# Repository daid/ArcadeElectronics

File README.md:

ArcadeElectronics
=================

V-USB based Electronics board for Arcade controls

Features
========
* V-USB based USB Interface emulating a mouse, keyboard and gamepad with full configuration of button mapping (no drivers required)
* 4 way digital joystick + 7 button connections. 4 way joystick inputs can also be used for analogue joystick.
* 16 LED output pins (max current total 200mA) which can also be used as inputs. And 8 are also mapped wired to 1A higher power outputs with external power supply (optional hardware)
* RFM12 wireless transiever (optional hardware) allows communication with other controllers and building of wireless controllers with 2 boards.
* Full open-source hardware & open-source software - Build with Free-Open-Source tools (KiCAD & AVR-GCC)
* ISP header to program the AVR (reset line can be cut and re-wired to have the board function as an programmer on the same header)
* USB-micro or USB-B connector depending on your taste
* Different small board designs, depending on your requirements:
	* 100x50mm: Fully featured, has option for 16 LED outputs, of which 8 can be configured for high power. Has wireless RFM12 option. 4 direction inputs, 7 button inputs
	* 50x50mm: Only base features with screw connectors. 4 direction inputs, 7 button inputs.
	* 50x25mm: Only base features with pin connectors. 4 direction inputs, 7 button inputs 
	* 25x25mm: Only base features with pin connectors, components on both sides. 4 direction inputs, 7 button inputs 

Organization
============
The following directories are in this project:
* Electronics - Contain the KiCAD design files
* Software/firmware/bootloader - Modified HIDBoot
* Software/firmware/arcade - Main firmware for the Arcade controller
* Software/computer/commandline - Commandline application to change the controller configuration, and control the LEDs
* Software/computer/lib - Library shared between different applications for custom commands to the ArcadeController
* Software/computer/gui_test - SDL based application to verify the Keyboard/Joystick/Mouse inputs

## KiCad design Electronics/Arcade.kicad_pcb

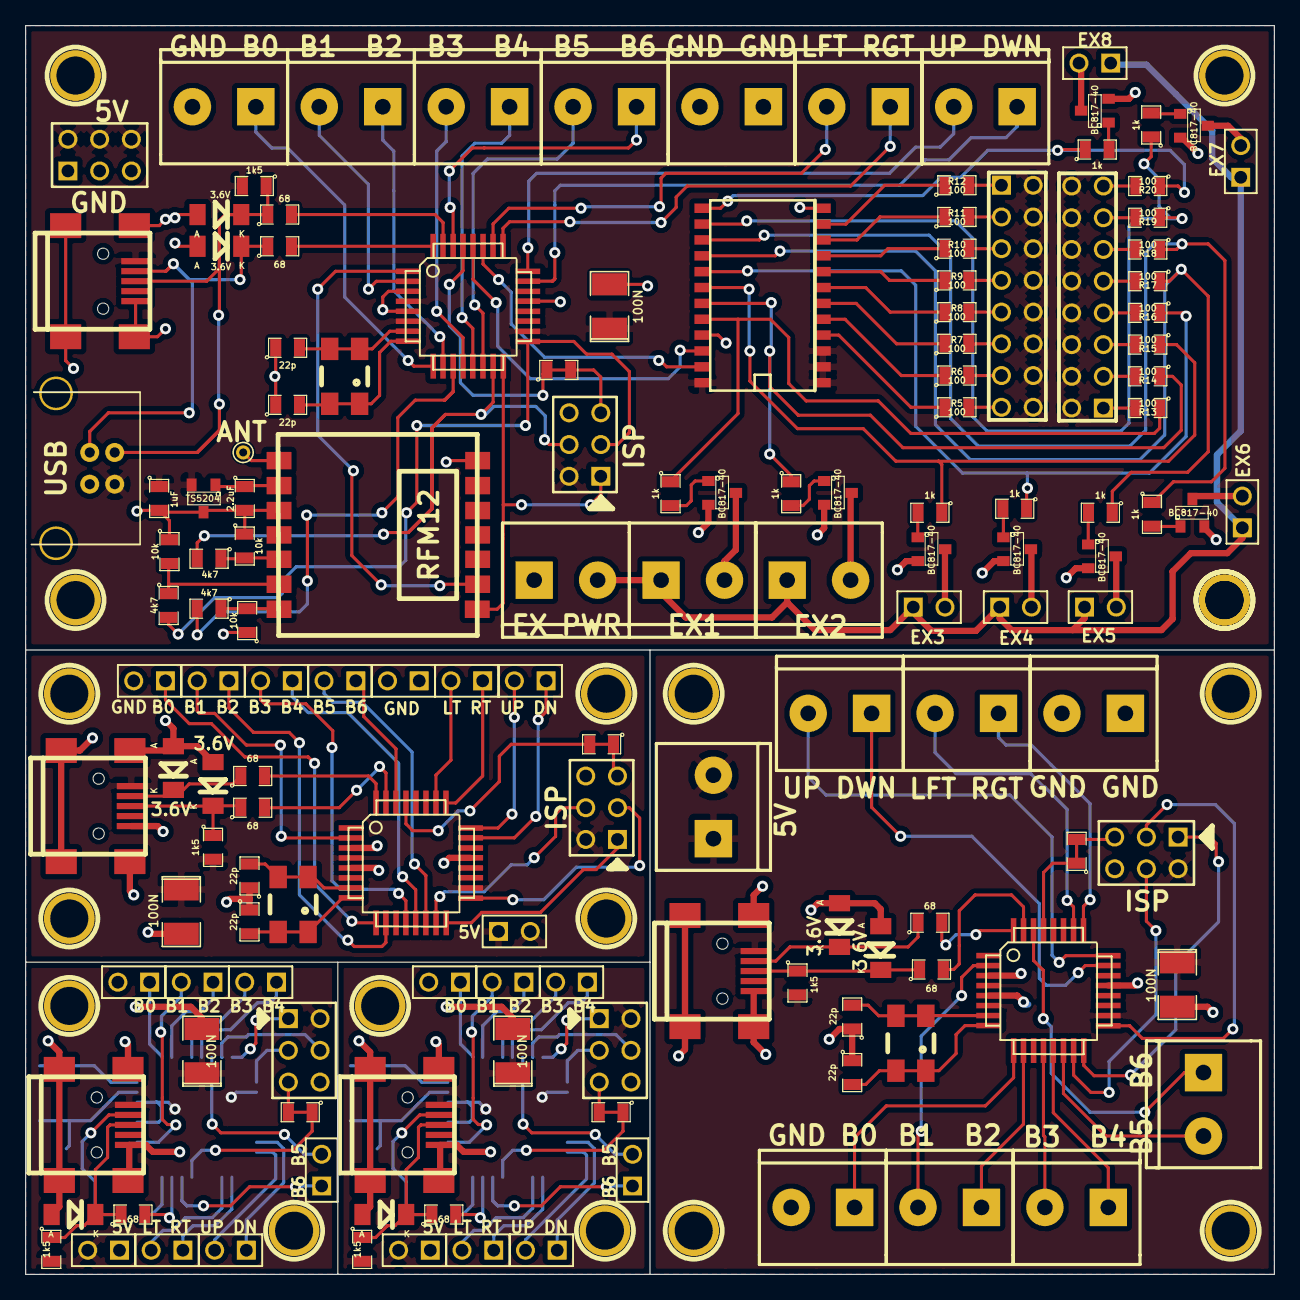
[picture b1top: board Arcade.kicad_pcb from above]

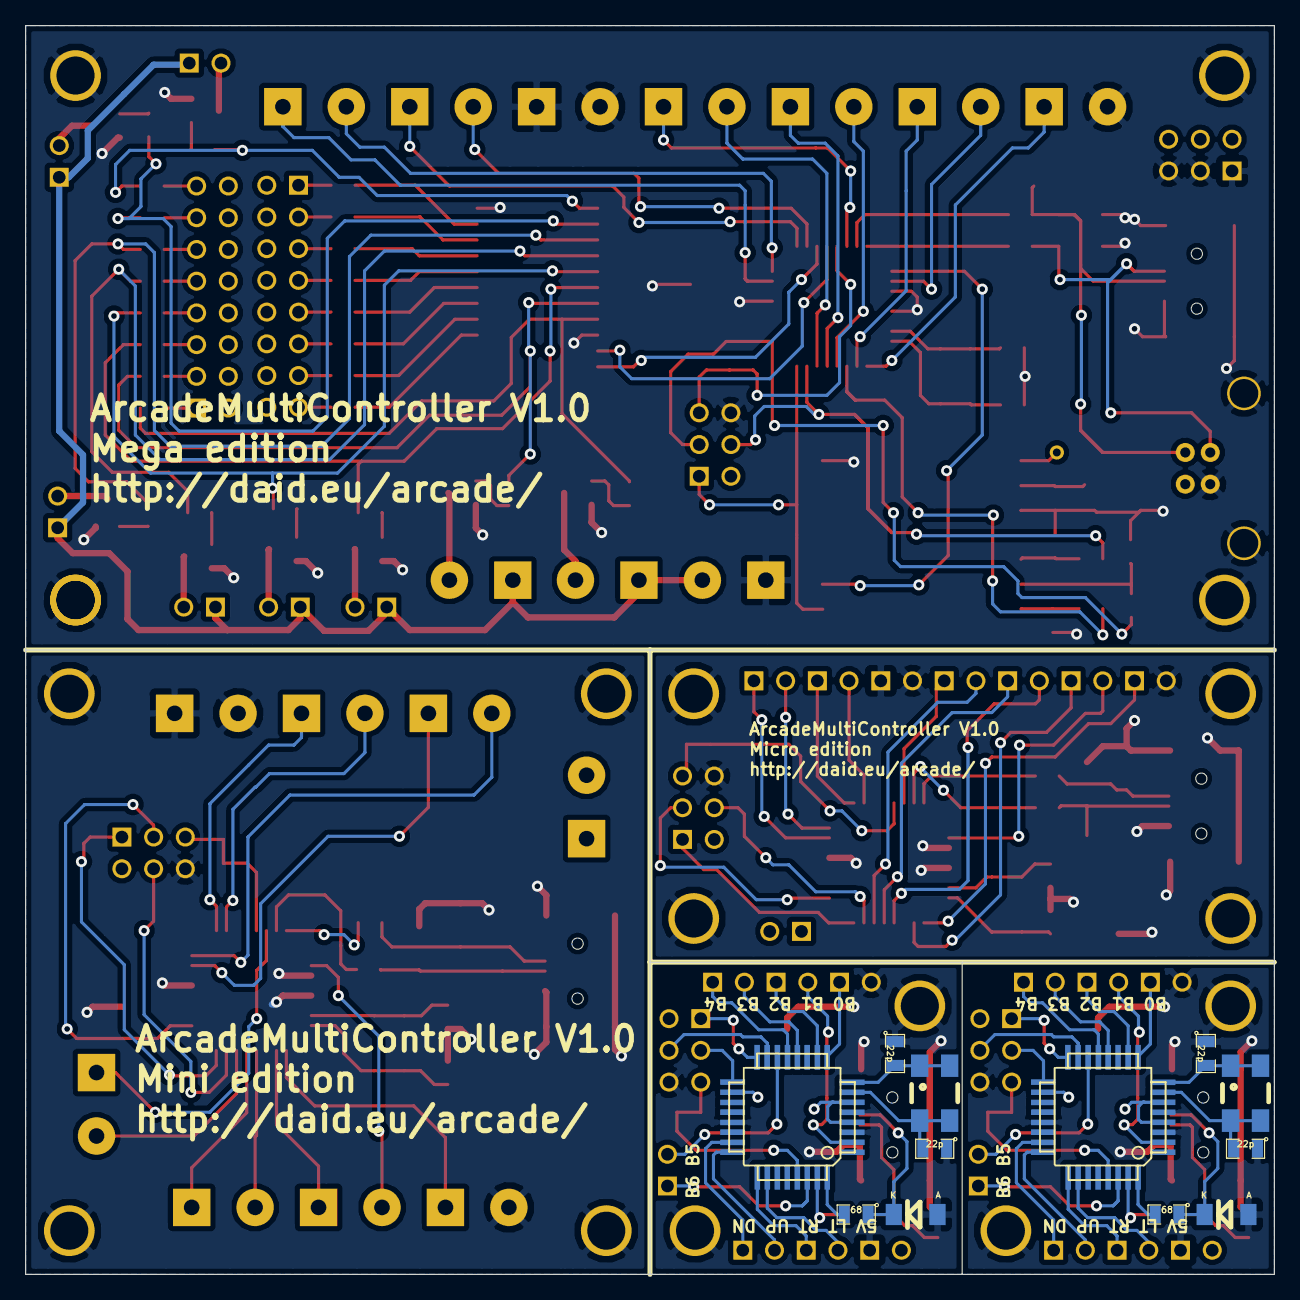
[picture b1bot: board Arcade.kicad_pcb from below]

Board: 2 copper layers, 100.0 x 100.0 mm, 176 parts (12 on the bottom side), 144 nets.

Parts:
1PIN, 1PIN#2, 1PIN#3, 1PIN#4, 1PIN#5, 1PIN#6, 1PIN#7, 1PIN#8, 1PIN#9, 1PIN#10, 1PIN#11, 1PIN#12, 1PIN#13, 1PIN#14, 1PIN#15, 1PIN#16, 1PIN#17: P***; 1pin
C1, C2, C6, C7, C9, C10, C12, C12#2, C13, C13#2: 22p; SM0805
C3, C8, C11, C14, C14#2: 100N; SM1210L
C4: 1uF; SM0805
C5: 2.2uF; SM0805
CON1, CON2, CON3, CON4, CON4#2: USB-MINI-B; USB_MINI_B
D1, D2, D3, D4, D5, D6, D7, D7#2, D8, D8#2: 3.6V; Diode-MiniMELF_Standard_RevA_27July2010
IC1, IC2, IC3, IC4, IC4#2: ATMEGA8A-A; TQFP32
J1: USB; USB_B_SHORT
P1, P22, P30, P40, P40#2: ISP; pin_array_3x2
P2, P23: UP DWN; mors_2p
P3, P24: LFT RGT; mors_2p
P4, P25: GND GND; mors_2p
P5, P26: B5 B6; mors_2p
P6, P27: B3 B4; mors_2p
P7, P28: B1 B2; mors_2p
P8, P29: GND B0; mors_2p
P9: ANT; PINTST
P10, P11: CONN_8X2; pin_array_8x2
P12: EX1; mors_2p
P13: EX_PWR; mors_2p
P14: CONN_3X2; pin_array_3x2
P15: EX2; mors_2p
P16: EX3; PIN_ARRAY_2X1
P17: EX4; PIN_ARRAY_2X1
P18: EX5; PIN_ARRAY_2X1
P19: EX6; PIN_ARRAY_2X1
P20: EX7; PIN_ARRAY_2X1
P21: EX8; PIN_ARRAY_2X1
P31, P41, P41#2: UP DWN; PIN_ARRAY_2X1
P32, P42, P42#2: LFT RGT; PIN_ARRAY_2X1
P33: GND GND; PIN_ARRAY_2X1
P34, P44, P44#2: B5 B6; PIN_ARRAY_2X1
P35, P45, P45#2: B3 B4; PIN_ARRAY_2X1
P36, P46, P46#2: B1 B2; PIN_ARRAY_2X1
P37, P47, P47#2: GND B0; PIN_ARRAY_2X1
P38, P48, P48#2: 5V; PIN_ARRAY_2X1
P39: 5V; mors_2p
Q1, Q2, Q3, Q4, Q5, Q6, Q7, Q8: BC817-40; SOT23
R1, R35, R39, R43, R43#2: 1k5; SM0805
R2, R3, R36, R37, R40, R41, R44, R44#2, R45, R45#2: 68; SM0805
R4, R38, R42, R46, R46#2: 0; SM0805
R5, R6, R7, R8, R9, R10, R11, R12, R13, R14, R15, R16, R17, R18, R19, R20: 100; SM0805
R21, R22, R23: 4k7; SM0805
R24, R25, R26: 10k; SM0805
R27, R28, R29, R30, R31, R32, R33, R34: 1k; SM0805
U1: PCA9532; SO24E
U2: RFM12
U3: TS5204; SOT23
X1, X2, X3, X4, X4#2: 16Mhz; Crystal_SMD_0603_4Pads_RevA_09Aug2010

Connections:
/B0: IC1.9, P8.1
/B0_2: IC2.9, P29.1
/B0_3: IC3.9, P37.1
/B0_4: IC4.9, IC4#2.9, P47.1, P47#2.1
/B1: IC1.2, P7.2
/B1_2: IC2.2, P28.2
/B1_3: IC3.2, P36.2
/B1_4: IC4.2, IC4#2.2, P46.2, P46#2.2
/B2: IC1.10, P7.1
/B2_2: IC2.10, P28.1
/B2_3: IC3.10, P36.1
/B2_4: IC4.10, IC4#2.10, P46.1, P46#2.1
/B3: IC1.12, P6.2
/B3_2: IC2.12, P27.2
/B3_3: IC3.12, P35.2
/B3_4: IC4.12, IC4#2.12, P45.2, P45#2.2
/B4: IC1.13, P6.1
/B4_2: IC2.13, P27.1
/B4_3: IC3.13, P35.1
/B4_4: IC4.13, IC4#2.13, P45.1, P45#2.1
/B5: IC1.14, P5.2
/B5_2: IC2.14, P26.2
/B5_3: IC3.14, P34.2
/B5_4: IC4.14, IC4#2.14, P44.2, P44#2.2
/B6: IC1.30, P5.1
/B6_2: IC2.30, P26.1
/B6_3: IC3.30, P34.1
/B6_4: IC4.30, IC4#2.30, P44.1, P44#2.1
/BTN_DOWN: IC1.23, P2.1
/BTN_DOWN_2: IC2.23, P23.1
/BTN_DOWN_3: IC3.23, P31.1
/BTN_DOWN_4: IC4.23, IC4#2.23, P41.1, P41#2.1
/BTN_LEFT: IC1.26, P3.2
/BTN_LEFT_2: IC2.26, P24.2
/BTN_LEFT_3: IC3.26, P32.2
/BTN_LEFT_4: IC4.26, IC4#2.26, P42.2, P42#2.2
/BTN_RIGHT: IC1.25, P3.1
/BTN_RIGHT_2: IC2.25, P24.1
/BTN_RIGHT_3: IC3.25, P32.1
/BTN_RIGHT_4: IC4.25, IC4#2.25, P42.1, P42#2.1
/BTN_UP: IC1.24, P2.2
/BTN_UP_2: IC2.24, P23.2
/BTN_UP_3: IC3.24, P31.2
/BTN_UP_4: IC4.24, IC4#2.24, P41.2, P41#2.2
/EX1: P12.2, Q2.3
/EX1_OUT: R13.1, R30.1, U1.20
/EX2: P15.2, Q3.3
/EX2_OUT: R14.1, R29.1, U1.19
/EX3: P16.2, Q4.3
/EX3_OUT: R15.1, R28.1, U1.18
/EX4: P17.2, Q5.3
/EX4_OUT: R16.1, R27.1, U1.17
/EX5: P18.2, Q1.3
/EX5_OUT: R17.1, R31.1, U1.16
/EX6: P19.2, Q6.3
/EX6_OUT: R18.1, R32.1, U1.15
/EX7: P20.2, Q7.3
/EX7_OUT: R19.1, R33.1, U1.14
/EX8: P21.2, Q8.3
/EX8_OUT: R20.1, R34.1, U1.13
/EX_PWR: P12.1, P13.2, P15.1, P16.1, P17.1, P18.1, P19.1, P20.1, P21.1
/MISO: IC1.16, P1.1, U2.1
/MISO_2: IC2.16, P22.1
/MISO_3: IC3.16, P30.1
/MISO_4: IC4.16, IC4#2.16, P40.1, P40#2.1
/MOSI: IC1.15, P1.4, R23.2
/MOSI_2: IC2.15, P22.4
/MOSI_3: IC3.15, P30.4
/MOSI_4: IC4.15, IC4#2.15, P40.4, P40#2.4
/RESET: IC1.29, P1.5, R4.1, R4.2
/RESET_2: IC2.29, P22.5, R38.1, R38.2
/RESET_3: IC3.29, P30.5, R42.1, R42.2
/RESET_4: IC4.29, IC4#2.29, P40.5, P40#2.5, R46.1, R46.2, R46#2.1, R46#2.2
/RF_IRQ: IC1.1, U2.2
/RF_SEL: IC1.11, R21.2
/SCK: IC1.17, P1.3, R22.2
/SCK_2: IC2.17, P22.3
/SCK_3: IC3.17, P30.3
/SCK_4: IC4.17, IC4#2.17, P40.3, P40#2.3
/SCL: IC1.28, U1.22
/SDA: IC1.27, U1.23
/USB_D+: IC1.32, R2.2
/USB_D+_2: IC2.32, R36.2
/USB_D+_3: IC3.32, R40.2
/USB_D+_4: IC4.32, IC4#2.32, R44.2, R44#2.2
/USB_D-: IC1.31, R3.2
/USB_D-_2: IC2.31, R37.2
/USB_D-_3: IC3.31, R41.2
/USB_D-_4: IC4.31, IC4#2.31, R45.2, R45#2.2
/V3.3: C5.1, U2.9, U3.1
GND: 1PIN.1, 1PIN#2.1, 1PIN#3.1, 1PIN#4.1, 1PIN#5.1, 1PIN#6.1, 1PIN#7.1, 1PIN#8.1, 1PIN#9.1, 1PIN#10.1, 1PIN#11.1, 1PIN#12.1, 1PIN#13.1, 1PIN#14.1, 1PIN#15.1, 1PIN#16.1, 1PIN#17.1, C1.1, C2.1, C3.2, C4.2, C5.2, C6.1, C7.1, C8.2, C9.1, C10.1, C11.2, C12.1, C12#2.1, C13.1, C13#2.1, C14.2, C14#2.2, CON1.5, CON1.6, CON1.7, CON1.8, CON1.9, CON2.5, CON2.6, CON2.7, CON2.8, CON2.9, CON3.5, CON3.6, CON3.7, CON3.8, CON3.9, CON4.5, CON4.6, CON4.7, CON4.8, CON4.9, CON4#2.5, CON4#2.6, CON4#2.7, CON4#2.8, CON4#2.9, D1.1, D2.1, D3.1, D4.1, D5.1, D6.1, D7.1, D7#2.1, D8.1, D8#2.1, IC1.3, IC1.5, IC1.21, IC2.3, IC2.5, IC2.21, IC3.3, IC3.5, IC3.21, IC4.3, IC4.5, IC4.21, IC4#2.3, IC4#2.5, IC4#2.21, J1.4, J1.5, J1.6, P1.6, P4.1, P4.2, P8.2, P13.1, P14.1, P14.3, P14.5, P22.6, P25.1, P25.2, P29.2, P30.6, P33.1, P33.2, P37.2, P40.6, P40#2.6, P47.2, P47#2.2, P48.1, P48#2.1, Q1.2, Q2.2, Q3.2, Q4.2, Q5.2, Q6.2, Q7.2, Q8.2, R24.1, R25.1, R26.1, U1.12, U1.21, U2.7, U2.10, U3.3
unnamed: C9.2, IC3.7, X3.2
unnamed: CON2.2, D3.2, R36.1
unnamed: C10.2, IC3.8, X3.1
unnamed: CON2.3, D4.2, R35.1, R37.1
unnamed: C6.2, IC2.7, X2.2
unnamed: C7.2, IC2.8, X2.1
unnamed: CON4.3, CON4#2.3, D8.2, D8#2.2, R43.1, R43#2.1, R45.1, R45#2.1
unnamed: CON4.2, CON4#2.2, D7.2, D7#2.2, R44.1, R44#2.1
unnamed: CON3.3, D6.2, R39.1, R41.1
unnamed: C12.2, C12#2.2, IC4.7, IC4#2.7, X4.2, X4#2.2
unnamed: C13.2, C13#2.2, IC4.8, IC4#2.8, X4.1, X4#2.1
unnamed: CON3.2, D5.2, R40.1
unnamed: R8.1, U1.7
unnamed: P10.1, R12.2
unnamed: R12.1, U1.11
unnamed: P10.3, R11.2
unnamed: R11.1, U1.10
unnamed: R10.1, U1.9
unnamed: R9.1, U1.8
unnamed: R7.1, U1.6
unnamed: R6.1, U1.5
unnamed: R5.1, U1.4
unnamed: P10.15, R5.2
unnamed: P10.13, R6.2
unnamed: P10.11, R7.2
unnamed: P10.9, R8.2
unnamed: P10.7, R9.2
unnamed: P10.5, R10.2
unnamed: C1.2, IC1.7, X1.2
unnamed: C2.2, IC1.8, X1.1
unnamed: P9.1, U2.8
unnamed: P11.15, R20.2
unnamed: Q4.1, R28.2
unnamed: P11.13, R19.2
unnamed: Q3.1, R29.2
unnamed: Q5.1, R27.2
unnamed: Q2.1, R30.2
unnamed: P11.9, R17.2
unnamed: P11.11, R18.2
unnamed: P11.5, R15.2
unnamed: P11.1, R13.2
unnamed: P11.3, R14.2
unnamed: P11.7, R16.2
unnamed: Q7.1, R33.2
unnamed: Q6.1, R32.2
unnamed: Q8.1, R34.2
unnamed: Q1.1, R31.2
unnamed: CON1.3, D2.2, J1.2, R1.1, R3.1
unnamed: CON1.2, D1.2, J1.3, R2.1
unnamed: R21.1, R26.2, U2.14
unnamed: R22.1, R25.2, U2.13
unnamed: R23.1, R24.2, U2.12
VCC: C3.1, C4.1, C8.1, C11.1, C14.1, C14#2.1, CON1.1, CON2.1, CON3.1, CON4.1, CON4#2.1, IC1.4, IC1.6, IC1.18, IC2.4, IC2.6, IC2.18, IC3.4, IC3.6, IC3.18, IC4.4, IC4.6, IC4.18, IC4#2.4, IC4#2.6, IC4#2.18, J1.1, P1.2, P10.2, P10.4, P10.6, P10.8, P10.10, P10.12, P10.14, P10.16, P11.2, P11.4, P11.6, P11.8, P11.10, P11.12, P11.14, P11.16, P14.2, P14.4, P14.6, P22.2, P30.2, P38.1, P38.2, P39.1, P39.2, P40.2, P40#2.2, P48.2, P48#2.2, R1.2, R35.2, R39.2, R43.2, R43#2.2, U1.1, U1.2, U1.3, U1.24, U3.2

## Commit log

2013-07-29 Added V1.0 electronics version. Untested.
2013-07-30 Update the readme a bit.
2013-07-30 Add test tool that shows keyboard/mouse input (need to add joystick input)
2013-07-31 Create gh-pages branch via GitHub
